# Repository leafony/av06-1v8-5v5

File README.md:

# Leafony AV06 1.8V〜5.5V

Leafony用電源リーフ「AV06 1.8V〜5.5V」のハードウェア設計データです。外部電源から3.3Vを生成する昇降圧回路と、入力電圧を監視するADC回路を備えています。

KiCadの回路図・基板データに加え、専用ライブラリ、3Dモデル、面付け基板、製造用データを収録しています。

## 基板の3D画像

| Top（表面） | Bottom（裏面・部品面） |
| :---: | :---: |
|  |  |

単体基板のKiCadデータから生成した3Dレンダリングです。

## 主な構成

| 機能 | 構成 |
| --- | --- |
| 電源入力 | JST PHコネクタ `S2B-PH-SM4-TB` |
| 電源スイッチ | `CUS-12TB`、ロードスイッチ `TPS22917DBV` |
| 昇降圧電源 | `TPS631010YBGR`による3.3V生成 |
| 出力側ダイオード | 理想ダイオード `MAX40200ANS` |
| 電圧監視 | I²C ADC `ADC081C027CIMK/NOPB`で、分圧した`VBATT`を測定 |
| Leafony接続 | Leafony Bus経由の3.3V供給とI²C接続 |
| 基板 | 4層、板厚0.8mm（単体基板の設計設定） |

## ファイル構成

主要なファイルは`kicad/leafony-av06-1v8-5v5/`にあります。

```text
kicad/leafony-av06-1v8-5v5/
├── leafony-av06-1v8-5v5.kicad_pro       # KiCadプロジェクト
├── leafony-av06-1v8-5v5.kicad_sch       # ルート回路図
├── leafony-av06-1v8-5v5.kicad_pcb       # 単体基板
├── input_conn.kicad_sch                # 電源入力・スイッチ
├── buck_boost.kicad_sch                # 昇降圧電源
├── adc.kicad_sch                       # 電圧監視ADC
├── leafony_bus.kicad_sch               # Leafony Bus接続
├── sym-lib-table                      # シンボルライブラリ設定
├── fp-lib-table                       # フットプリントライブラリ設定
├── lib/
│   ├── Leafony.kicad_sym               # 専用シンボル
│   ├── Leafony.pretty/                 # 専用フットプリント
│   └── 3dmodels/                      # 部品の3Dモデル
└── panelized/
    ├── leafony-av06-1v8-5v5-panelized.kicad_pro
    ├── leafony-av06-1v8-5v5-panelized.kicad_pcb
    ├── bom-leafony-av06-1v8-5v5-pcbgogo.xlsx
    └── Gerber/                        # Gerber・ドリル・部品配置データ
```

## KiCadで開く

ルート回路図・子回路図・単体基板はKiCad 10.0形式で保存されています。編集にはKiCad 10.0以降を使用してください。面付け基板はKiCad 8.0形式で保存されています。

1. このディレクトリ一式を取得します。
2. KiCadで[`leafony-av06-1v8-5v5.kicad_pro`](kicad/leafony-av06-1v8-5v5/leafony-av06-1v8-5v5.kicad_pro)を開きます。
3. プロジェクトマネージャーから回路図エディター、または基板エディターを開きます。
4. 回路図では、ルートシート内の各階層シートを開いて回路ブロックを確認します。

専用ライブラリは`fp-lib-table`と`sym-lib-table`に登録済みです。`${KIPRJMOD}/lib/`を参照するため、`lib/`を含むディレクトリ構成を維持してください。標準部品の3D表示にはKiCad標準3Dモデルも必要です。

## 製造用データ

[`panelized/`](kicad/leafony-av06-1v8-5v5/panelized/)に、面付け基板とPCBGOGO向け部品表を収録しています。[`Gerber/`](kicad/leafony-av06-1v8-5v5/panelized/Gerber/)には、各層のGerber、PTH／NPTHドリル、表裏の部品配置データ（`.pos`）があります。

設計変更後は、回路図のERCと基板のDRCを確認し、面付け基板・部品表・製造用データにも変更を反映してください。

## Gitで管理するファイル

回路図、基板、プロジェクト設定、専用ライブラリ、3Dモデル、製造用データを管理対象とします。ルートの`.gitignore`では、KiCadのローカル設定（`.kicad_prl`）、ロック、自動保存、バックアップ、OSやエディターの一時ファイルを除外しています。

KiCadプロジェクト内の既存の`.gitignore`には、ネットリスト、外部配線ツールの中間ファイル、XML／CSV出力の除外設定もあります。

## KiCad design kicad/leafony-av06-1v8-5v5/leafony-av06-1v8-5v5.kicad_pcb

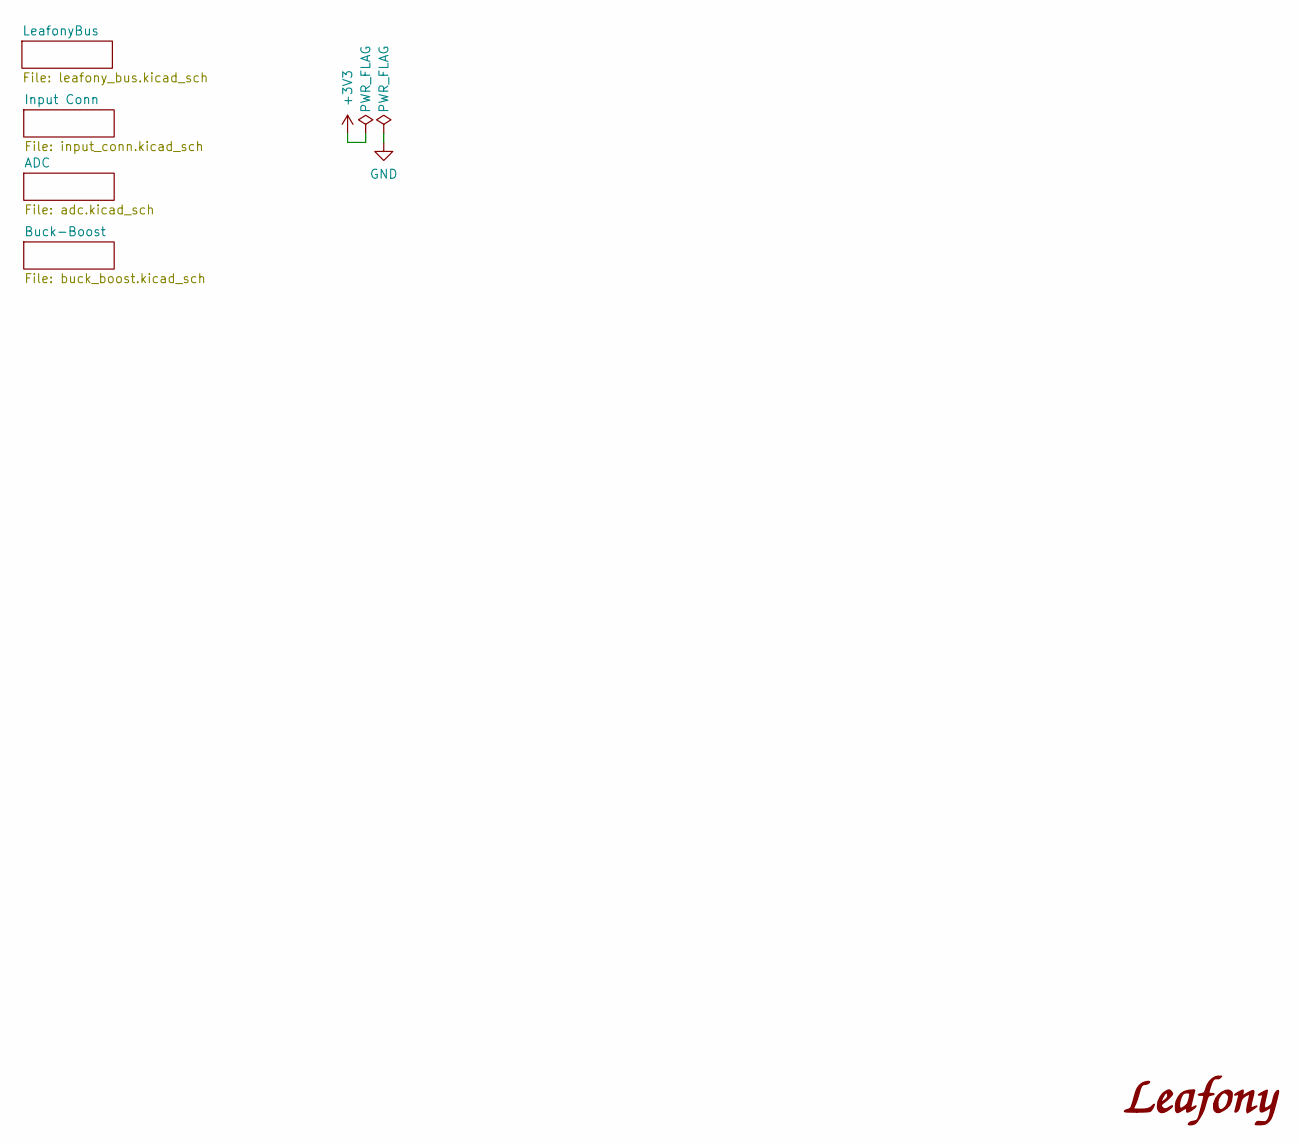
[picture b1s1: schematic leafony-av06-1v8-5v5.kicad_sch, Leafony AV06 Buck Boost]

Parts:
LOGO1: LOGO; LEAFONY_LOGO

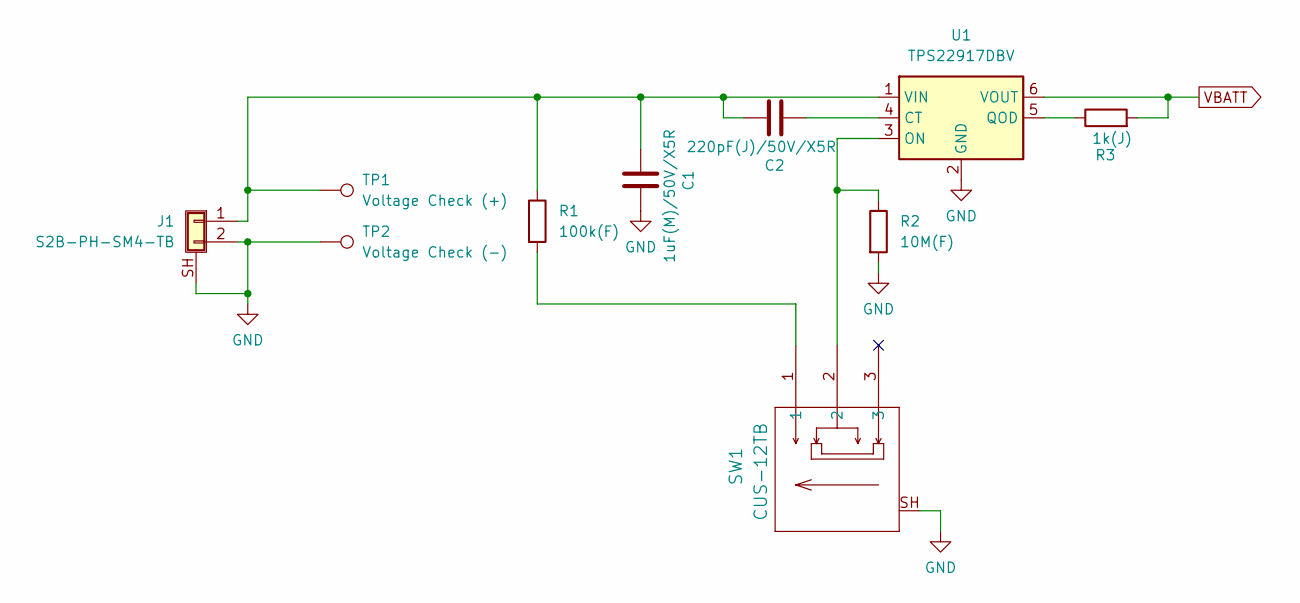
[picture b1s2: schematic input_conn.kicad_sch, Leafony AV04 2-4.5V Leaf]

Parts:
C1: 1uF(M)/50V/X5R; C_0402_1005Metric
C2: 220pF(J)/50V/X5R; C_0402_1005Metric
J1: S2B-PH-SM4-TB; JST_PH_S2B-PH-SM4-TB_1x02-1MP_P2.00mm_Horizontal
R1: 100k(F); R_0402_1005Metric
R2: 10M(F); R_0402_1005Metric
R3: 1k(J); R_0402_1005Metric
SW1: CUS-12TB; CUS-12TB_NDC
TP1: Voltage Check (+); TestPoint_Pad_D1.0mm
TP2: Voltage Check (-); TestPoint_Pad_D1.0mm
U1: TPS22917DBV; SOT-23-6

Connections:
GND: C1.1, J1.2, J1.SH (Shield), R2.2, SW1.SH, TP2.1, U1.2 (GND); also elsewhere on the board
unnamed: C1.2, C2.1, J1.1, R1.1, TP1.1, U1.1 (VIN)
unnamed: R1.2, SW1.1
unnamed: C2.2, U1.4 (CT)
unnamed: R2.1, SW1.2, U1.3 (ON)
unnamed: R3.1, U1.5 (QOD)
VBATT: R3.2, U1.6 (VOUT); also elsewhere on the board

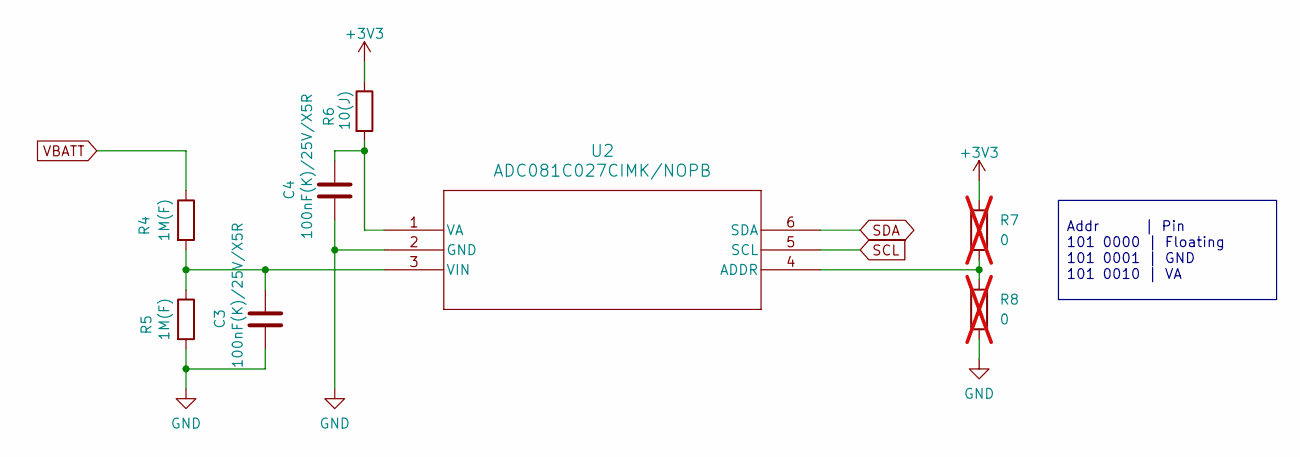
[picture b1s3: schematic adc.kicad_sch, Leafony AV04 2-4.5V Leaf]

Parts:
C3, C4: 100nF(K)/25V/X5R; C_0402_1005Metric
R4, R5: 1M(F); R_0402_1005Metric
R6: 10(J); R_0402_1005Metric
R7, R8: 0; R_0402_1005Metric; not fitted
U2: ADC081C027CIMK/NOPB; SOT-23-6

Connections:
+3V3: R6.1, R7.1; also elsewhere on the board
GND: C3.2, C4.2, R5.2, R8.2, U2.2 (GND); also elsewhere on the board
unnamed: R7.2, R8.1, U2.4 (ADDR)
unnamed: C4.1, R6.2, U2.1 (VA)
unnamed: C3.1, R4.2, R5.1, U2.3 (VIN)
SCL: U2.5 (SCL); also elsewhere on the board
SDA: U2.6 (SDA); also elsewhere on the board
VBATT: R4.1; also elsewhere on the board

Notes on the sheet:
Addr | Pin 101 0000 | Floating 101 0001 | GND 101 0010 | VA

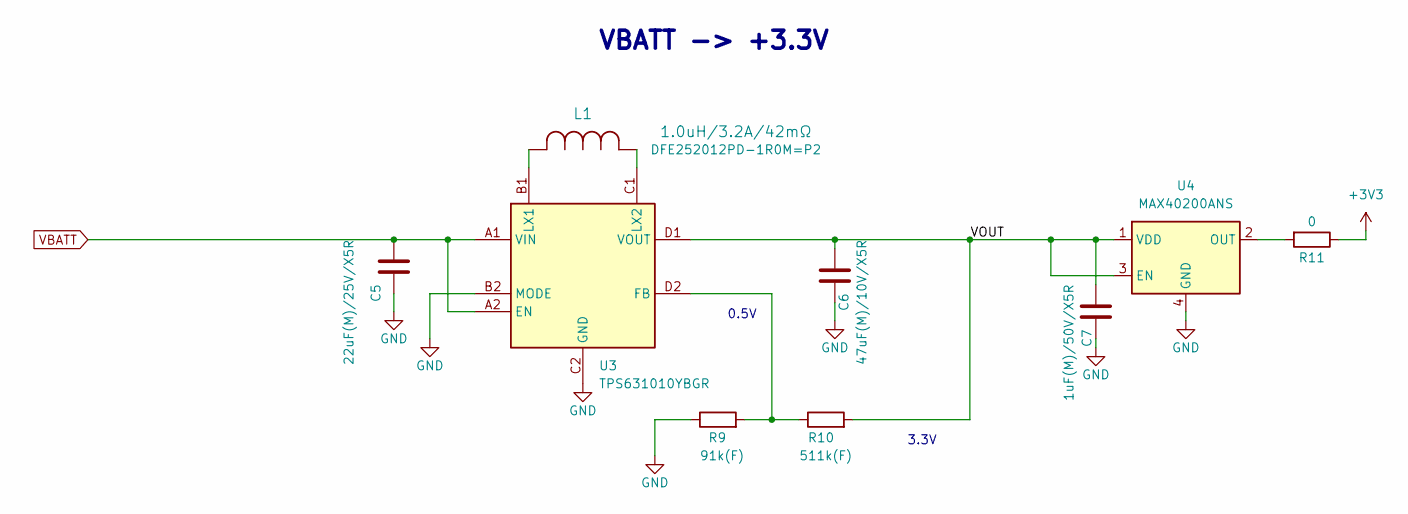
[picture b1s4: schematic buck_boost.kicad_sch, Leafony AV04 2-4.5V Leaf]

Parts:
C5: 22uF(M)/25V/X5R; C_0805_2012Metric
C6: 47uF(M)/10V/X5R; C_0805_2012Metric
C7: 1uF(M)/50V/X5R; C_0402_1005Metric
L1: 1.0uH/3.2A/42mΩ; DFE2HCAH1R0MJ0L
R9: 91k(F); R_0402_1005Metric
R10: 511k(F); R_0402_1005Metric
R11: 0; R_0402_1005Metric
U3: TPS631010YBGR; TPS631010; Manufacturer_Part_Number TPS631010YBGR
U4: MAX40200ANS; WLP-4_0.73x0.73mm_Layout2x2_P0.35mm_Ball0.22mm_Pad0.2mm

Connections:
+3V3: R11.1; also elsewhere on the board
/Buck-Boost/VOUT: C6.1, C7.1, R10.2, U3.D1 (VOUT), U4.1 (VDD), U4.3 (EN)
GND: C5.2, C6.2, C7.2, R9.1, U3.B2 (MODE), U3.C2 (GND), U4.4 (GND); also elsewhere on the board
unnamed: R9.2, R10.1, U3.D2 (FB)
unnamed: L1.2, U3.B1 (LX1)
unnamed: L1.1, U3.C1 (LX2)
unnamed: R11.2, U4.2 (OUT)
VBATT: C5.1, U3.A1 (VIN), U3.A2 (EN); also elsewhere on the board

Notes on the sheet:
0.5V
3.3V
VBATT -> +3.3V

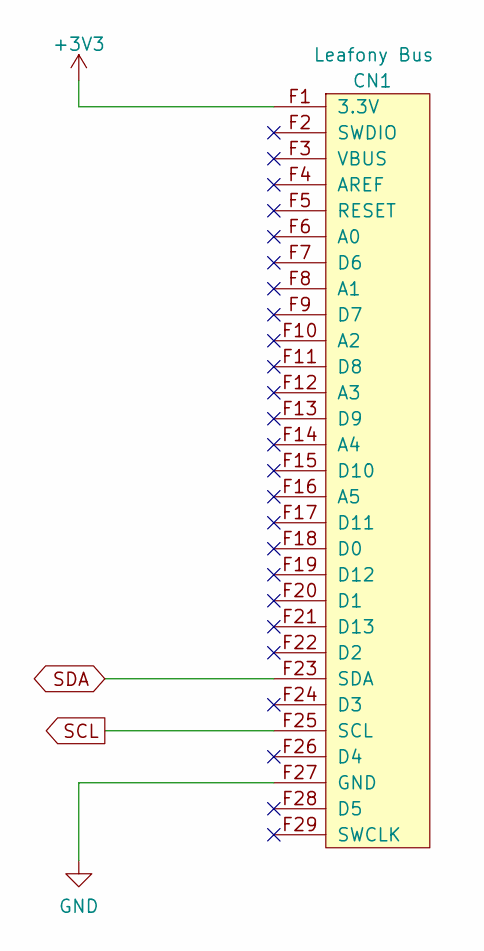
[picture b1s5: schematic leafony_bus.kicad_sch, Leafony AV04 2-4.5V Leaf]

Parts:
CN1: Leafony Bus; CN_F29

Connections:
+3V3: CN1.F1 (3.3V); also elsewhere on the board
GND: CN1.F27 (GND); also elsewhere on the board
SCL: CN1.F25 (SCL); also elsewhere on the board
SDA: CN1.F23 (SDA); also elsewhere on the board

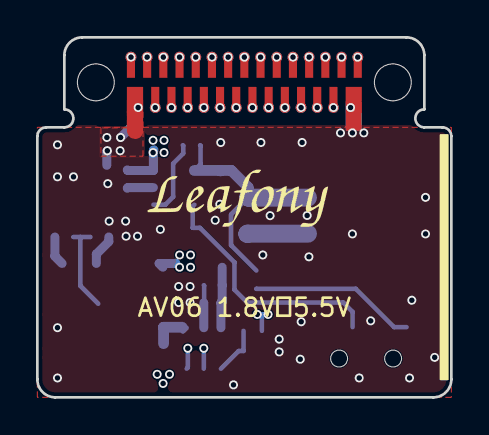
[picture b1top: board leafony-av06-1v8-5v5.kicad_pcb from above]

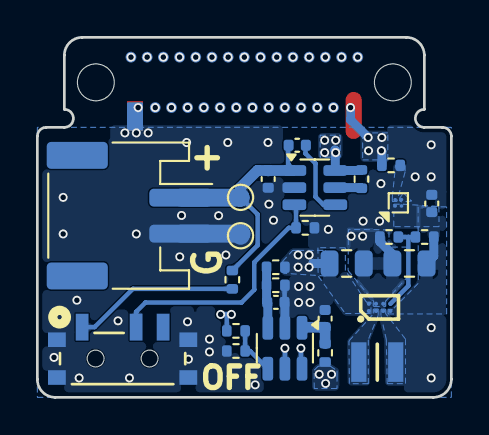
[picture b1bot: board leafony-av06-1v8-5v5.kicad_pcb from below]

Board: 4 copper layers, 23.0 x 20.0 mm, 29 parts (27 on the bottom side), 18 nets.

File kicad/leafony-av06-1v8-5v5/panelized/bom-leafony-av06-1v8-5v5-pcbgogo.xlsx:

|  |  | Leafony AV06 1.8V〜5.5V 1PCS BOM
Item # | *Ref Des | *Qty | Manufacturer | *Mfg Part # | Description / Value | *Package | Type | Your Instructions / Notes
1 | C1, C7 | 2 | Murata Electronics | GRM155R61H105ME05D | CAP CER 1UF 50V X5R 0402 | 0402 | SMD
2 | C2 | 1 | Murata Electronics | GRM1555C1H221JA01D | CAP CER 200pF 50V C0G 0402 | 0402 | SMD
3 | C3, C4 | 2 | Murata Electronics | GRM155R71H104KE14D | CAP CER 0.1UF 50V X7R 0402 | 0402 | SMD
4 | C5 | 1 | Murata Electronics | GRM21BR61E226ME44L | CAP CER 22UF 25V X5R 0805 | 0805 | SMD
5 | C6 | 1 | Murata Electronics | GRM21BR61A476ME15L | CAP CER 47UF 10V X5R 0805 | 0805 | SMD
6 | J1 | 1 | JST Sales America Inc. | S2B-PH-SM4-TB | CONN HEADER SMD R/A 2POS 2MM | 1x2pin conn | SMD
7 | L1 | 1 | Murata Electronics | DFE252012PD-1R0M=P2 | FIXED IND 1UH 3.2A 0.042OHM SMD | 1008 | SMD
8 | R1 | 1 | YAGEO | RC0402FR-07100KL | RES 100K OHM 1% 1/16W 0402 | 0402 | SMD
9 | R2 | 1 | YAGEO | RC0402FR-0710ML | RES 10M OHM 1% 1/16W 0402 | 0402 | SMD
10 | R3 | 1 | YAGEO | RC0402FR-071KL | RES 1K OHM 1% 1/16W 0402 | 0402 | SMD
11 | R4, R5 | 2 | YAGEO | RC0402FR-071ML | RES 1M OHM 1% 1/16W 0402 | 0402 | SMD
12 | R6 | 1 | YAGEO | RC0402FR-0710RL | RES 10 OHM 1% 1/16W 0402 | 0402 | SMD
13 | R7, R8 | 0 | ~ | ~ | ~ | ~ | ~
14 | R9 | 1 | YAGEO | RC0402FR-0791KL | RES 91K OHM 1% 1/16W 0402 | 0402 | SMD
15 | R10 | 1 | YAGEO | RC0402FR-07511KL | RES 511K OHM 1% 1/16W 0402 | 0402 | SMD
16 | R11 | 1 | YAGEO | RC0402JR-070RL | RES 0 OHM JUMPER 1/16W 0402 | 0402 | SMD
17 | SW1 | 1 | Nidec Components Corporation | CUS-12TB | SWITCH SLIDE SPDT 300MA 4V | CUS-12TB | SMD
18 | U1 | 1 | Texas Instruments | TPS22917DBVR | IC PWR SWITCH P-CHAN 1:1 SOT23-6 | SOT23-6 | SMD
19 | U2 | 1 | Texas Instruments | ADC081C027CIMK/NOPB | IC ADC 8BIT SAR TSOT23-6 | SOT23-6 | SMD
20 | U3 | 1 | Texas Instruments | TPS631010YBGR | IC REG BUCK BST ADJ 1.5A 8DSBGA | 8-XFBGA | SMD
21 | U4 | 1 | Analog Devices Inc./Maxim Integrated | MAX40200ANS+T | IC DIODE CURRENT SWITCH 4WLP | 4WLP | SMD
